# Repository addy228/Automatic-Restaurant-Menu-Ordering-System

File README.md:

Board 1 : Atmega8 transmitter has LCD, keypad and RF Tx connected
Board 2 : Atmega8 reciever has LCD and RF Rx connected
Menu is displayed on board 1 for customers and when a particular order is chosen through the keypad input that order is displayed on board 2 LDC which is kept in the kitchen after confirmation

If confirmed then that input is then sent to the rx board through RF else if it is cancelled then the whole menu is displayed again.

Software simulation is also executed on Proteus (.pdsprj)

PCB designs on the two boards are also included with the flowchart of the entire process.

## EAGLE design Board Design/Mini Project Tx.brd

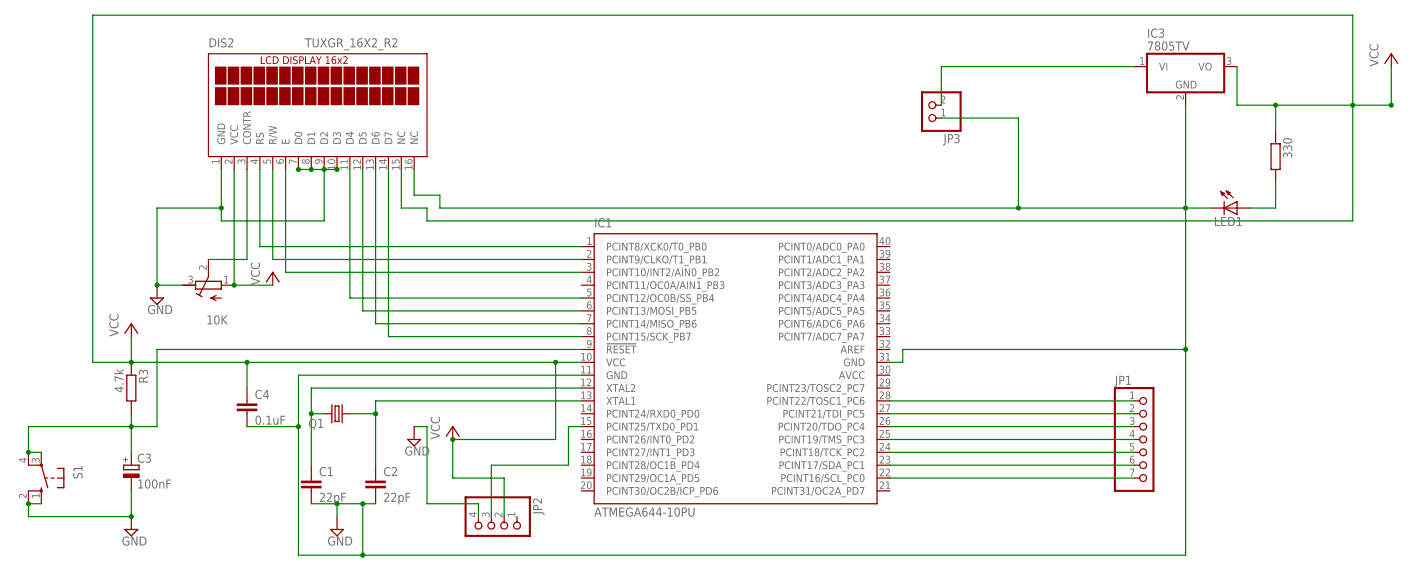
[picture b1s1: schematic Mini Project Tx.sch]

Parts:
10K: R-TRIMM64W; RTRIM64W
330: R-EU_0207/10; 0207/10
C1, C2: 22pF; C025-025X050
C3: 100nF; E2-4
C4: 0.1uF; C025-025X050
DIS2: TUXGR_16X2_R2
IC1: ATMEGA644-10PU; DIL40
IC3: 7805TV; TO220V
JP1: PINHD-1X7; 1X07
JP2: PINHD-1X4; 1X04
JP3: PINHD-1X2; 1X02
LED1: LED3MM
Q1: CRYSTALHC49S; HC49/S
R3: 4.7k; 0207/10
S1: 10-XX; B3F-10XX

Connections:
9V: IC3.1 (VI), JP3.2
AVCC: IC1.30 (AVCC)
GND: 10K.3 (E), C1.2, C2.2, C3.-, C4.2, DIS2.1 (GND), DIS2.7 (D0), DIS2.8 (D1), DIS2.9 (D2), DIS2.10 (D3), DIS2.16 (NC), IC1.11 (GND), IC1.31 (GND), IC3.2 (GND), JP2.4, JP3.1, LED1.K (C), S1.1 (S), S1.2 (S1)
unnamed: DIS2.4 (RS), IC1.1 (PCINT8/XCK0/T0_PB0)
unnamed: DIS2.5 (R/W), IC1.2 (PCINT9/CLKO/T1_PB1)
unnamed: DIS2.6 (E), IC1.3 (PCINT10/INT2/AIN0_PB2)
unnamed: DIS2.11 (D4), IC1.5 (PCINT12/OC0B/SS_PB4)
unnamed: DIS2.12 (D5), IC1.6 (PCINT13/MOSI_PB5)
unnamed: DIS2.13 (D6), IC1.7 (PCINT14/MISO_PB6)
unnamed: DIS2.14 (D7), IC1.8 (PCINT15/SCK_PB7)
unnamed: IC1.22 (PCINT16/SCL_PC0), JP1.7
unnamed: IC1.23 (PCINT17/SDA_PC1), JP1.6
unnamed: IC1.24 (PCINT18/TCK_PC2), JP1.5
unnamed: IC1.25 (PCINT19/TMS_PC3), JP1.4
unnamed: IC1.26 (PCINT20/TDO_PC4), JP1.3
unnamed: IC1.27 (PCINT21/TDI_PC5), JP1.2
unnamed: IC1.28 (PCINT22/TOSC1_PC6), JP1.1
unnamed: IC1.15 (PCINT25/TXD0_PD1), JP2.3
unnamed: C1.1, IC1.12 (XTAL2), Q1.2
unnamed: 10K.2 (S), DIS2.3 (CONTR)
unnamed: C2.1, IC1.13 (XTAL1), Q1.1
unnamed: 330.2, LED1.A
unnamed: C3.+, IC1.9 (!RESET), R3.2, S1.3, S1.4 (P1)
VCC: 10K.1 (A), 330.1, C4.1, DIS2.2 (VCC), DIS2.15 (NC), IC1.10 (VCC), IC3.3 (VO), JP2.2, R3.1

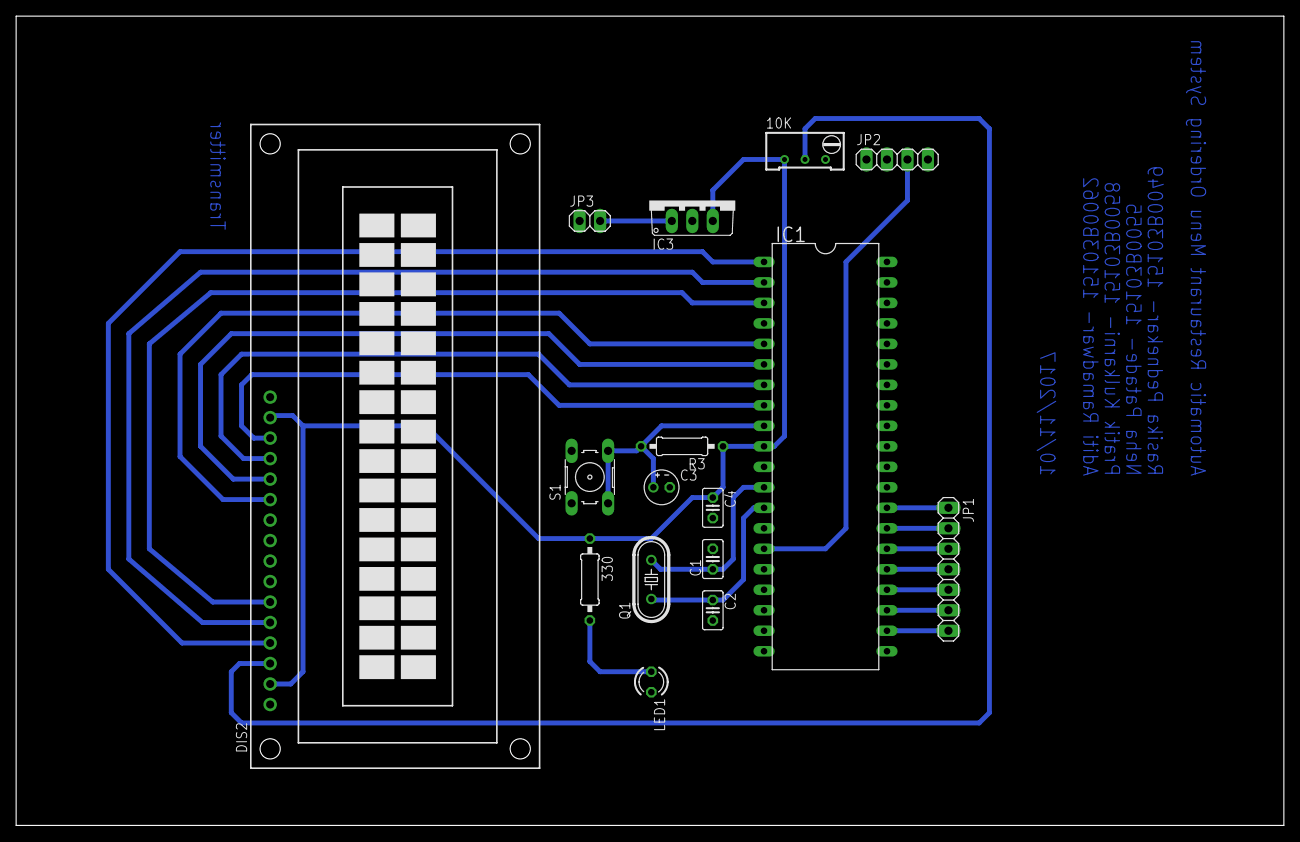
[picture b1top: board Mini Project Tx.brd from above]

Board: 2 copper layers, 157.2 x 100.3 mm, 16 parts (0 on the bottom side), 23 nets.
